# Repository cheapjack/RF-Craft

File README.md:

# RF-Craft

<br>
<br>

RF-Craft is a prototype Raspberry Pi [HAT](https://github.com/raspberrypi/hats) (**H**ardware **A**ttached on **T**op) arduino clone to send `mcpi` API commands wirelessly to a minecraft server. RF-Craft was built as part of Ross Dalziel's [OK Sparks Project](http://domesticscience.org.uk) and a spin-out from the [FACT](http://fact.co.uk/) [CloudMaker](http://www.fact.co.uk/projects/cloudmaker-making-minecraft-real.aspx) project research and inspired by resilient networks, the work of [Martin O'Hanlon](https://github.com/martinohanlon/mcpi) where `mcpi` is maintained via Mojang, [Shrimping.it](http://start.shrimping.it) and Minecraft modders worldwide. 

Full info from the [CloudMaker Repo](https://github.com/cheapjack/CloudMaker)

It is a board to help teach the **Internet of Things** and is inspired by the wider Minecraft community and culture where young people develop their own skillsets in order to take part in the games culture. In many ways it is the first game in mainstream consciousness where players take control of elements of the games infrastructure, independent of the original developer *Mojang*, often becoming their own **sysadmins** using custom servers for games they want to play and as a consequence, with considerable transferable skills in coding and IoT. 

Minecraft is not an open source project but the game community have, in a sense, opened up elements of it to allow extensive modding and creative hacking. This adhoc technical *culture* is what is the most valuable, not the game itself or even it's potential to educate, which is a consequence of this. After a good deal of research we've concluded that Minecraft is more representative of an independent learning culture and ecosystem on it's own and others borrowed terms and with it's own diversity. This is exciting but not necessarily always helpful to educators or learners.  

With experience, we think it should not really be confused with a universal *service* or *platform* that could be easily exploited for formal mainstream education.

Current owners, Microsoft are developing an education *platform* through [Minecraft Education](https://education.minecraft.net/). This is a very specific version of the game and so has very specific requirements to use. In this sense it *is* a platform, but like many platforms in the real world once you are on one its hard to jump to another without ladders, ropes or expensive jetpacks. We've all played on Parkour servers so we know how hard that can be!

We've tried to package up a range of resources, examples and hardware that could allow you to play with connecting versions of the game with the real world with sensors and buttons. 

Finding the right version of the game to experiment with is difficult and has it's own quite steep and confusing learning curve. We recommend keeping it simple and experimenting on a Pi. The Pi version is version 1.0 or something. It's simple and it's not changing. It's also free. There's an established community out there using the python [mcpi API](https://github.com/martinohanlon/mcpi) for it like [Martin O'Hanlon](https://github.com/martinohanlon/) and making cool stuff for it like [PatternCraft](http://patterncraft.co/).

So we've tried keeping it simple by making simple Raspeberry Pi HATS that can transmit and receive serial messages which you can parse into commands in the Raspberry Pi version of Minecraft you can make simpel HelloWorld Text Adventures, [Models of Railways](https://github.com/cheapjack/RF-Rail-Craft) or all the way up to interacting with [data](https://github.com/cheapjack/MoT), the [International Space Station](https://github.com/astro-pi/SpaceCRAFT) to punchard readers that make music just like PatternCraft.

This Open source Radio messaging system uses the [RFM69HW tranceiver chip](https://lowpowerlab.com/shop/rfm69hw)(based on the Lowpowerlab Moteino) and Frequency 868MHz to report to a central reciever to perform minecraft actions.

Its designed as a Minecraft-of-Things deluxe development board bridging the gap between Pi and Arduino without depending on both. One design parameter was to have good signal penetration through Victorian concrete and the concrete of many arts centres and/or schools for the [Ok Sparks!](http://slyrabbit.net/ok-sparks) project by [Domestic Science](http://domesticscience.org.uk). 

It was designed by artist [Ross Dalziel](http://cheapjack.org.uk) and open source engineer and technician in residence at [DoESLiverpool](http://doesliverpool.com) [Patrick Fenner AKA @DefProc](http://www.deferredprocrastination.co.uk/) and funded by [FACT](http://fact.co.uk/) and  [IT as a Utility (ITaaU) Network](http://www.itutility.ac.uk) for the [CloudMaker](http://www.fact.co.uk/projects/cloudmaker-making-minecraft-real.aspx) project following 2 years of research into the game as a social learning tool which we've since realised is, as we've said, more like a *culture*

### Features

 * On board button and LED, 
 * Digital input for a Dallas DS18B20 one-wire temperature sensor (with pullup resistor) and power rail 
 * 6 analog inputs broken out with power
 * Battery power breakout
 * Pi/External mode jumpers
 * IDE Free reciever/transmitter/Node programming switch
 * It can act as a powered HAT reciever/transmitter on board a Pi or as an independent battery powered arduino radio receiver or transmitter.
 * Open Source: Not cheap but open; but you can build them yourself!
 * Good singnal penetration through concrete castles
 * Need IoT Minecraft workshop & WiFi Down? Network Administrator at lunch? Got Pi, Got HAT Got RF-Craft - no problem!
 * Need radio arduinos for IoT prototype? Sick of Minecraft? Caps falling out of your shrimp? No problem use elsewhere!
 * Send Commands to a Receiver HAT and your Raspbians local Minecraft Pi Edition server
 * Send Commands to the Rasperry Juice Plugin on a CanaryMod server
 * Send Commands to the Rasperry Juice Plugin on `mc.fact.co.uk:25589`

### Message Format

messages are constructed of a `uint8_t` for node_id, followed by an `int8_t` for action

Possible action messages:

 * -1 : set_id
 *  0 : query_id
 *  1 : button press
 *  2 : error
 *  3 : OK

common key for messages: "changemechangeme"

all radios are in group: 87

Transmitter `node_ids` for buttons can be 1-100 but the onboard `node_id` switch can set them to 1-15 in Binary. By default with the big mode switch set to **EXT** the HAT is in transmitter mode and you need to set the `node_id` switch to 1-15. When the mode switch is set to **RPI** then the `node_id` is 254 which is a receiver. 

### Getting Started

The easiest thing to do is clone this repo into your `/home/pi` folder either with git or `wget https://github.com/cheapjack/RF-Craft/archive/master.zip` then `unzip`

You can install git with `sudo apt-get install git-core`
Then `git clone https://github.com/cheapjack/RF-Craft.git`

Then you can modify the `HelloPi.py` or `HelloSerial.py` `python 2.7` code and play with the transmitter and receiver boards pairs out of the box without even having to put the arduino sketches on. Unless you're making them yourselves from the details in the repo then well it's your box.

Then for full details you can read the nearby `GettingStarted.md` file

### RF-Craft

### Background

[The Minecraft Of Things](http://minecraftofthings.tumblr.com) sprang from research with [FACT](http://fact.co.uk/), [Dr Mark Wright](https://twitter.com/dr_mark_wright), [Adrian McEwen](http://www.mcqn.com/) and Paul Harter of [PrintCraft](http://www.printcraft.org/) funded by [IT as a Utility (ITaaU) Network](http://www.itutility.ac.uk) for the [CloudMaker](http://www.fact.co.uk/projects/cloudmaker-making-minecraft-real.aspx) project

Looking into how the Raspberry Pi could be used as an entry into embedded systems, physical computing and the Internet Of Things(IoT) we developed something that could be used in many contexts with simplicity at its core and with ideas that touched on data literacy, resilient networks and security. 

One of the big issues with use of Minecraft in education is networking often educators dont have the time or access to setup a school network for a wireless sensors to communicate with the game; we wanted to be able to be independent of this and for people to setup their own adhoc networks to follow how networks are used in real world applications.

For the final distribution of CloudMaker research we focussed on packaging up resources to help understand the Internet Of Things through Minecraft.

We took diverse approaches to reflect real IoT ecosystems; tried not to re-invent the wheel but point to fascinating education work going on in technology and post 'Maker' culture. 

We made simple arduino on a breadboard interfaces inspired by [Shrimping.It](http://start.shrimping.it) for interacting with minecraft over wired USB/FTDI adaptors, [ShrimpCraft](https://github.com/cheapjack/ShrimpCraft), a WiFi on a breadboard system [Cockle-Craft-of-Things](https://github.com/mcqn/cocklecraft-of-things) with MCQN Ltd. 

For RF-Craft we made a super robust custom PCB arduino RFM69 clone that has a more plug & python & play approach.

The receiver button pairs allow you to send wireless messages to a range of minecraft servers for augmented reality gaming and learning the Internet of Things (IoT) 

### Resources

This uses Martin O'Hanlon's [mcpi API](https://github.com/martinohanlon/mcpi) the Minecraft: Pi Edition API Python Library and his and Zhuowei's [Canary Raspberry Juice](https://github.com/martinohanlon/CanaryRaspberryJuice) plugin for use with FACT's CloudMaker Minecraft Server

### The FACT Server

The FACT CloudMaker Server is a server for prototyping multiplayer `mcpi` activity. Details for how to log on are at the [CloudMaker portal repo](https://github.com/cheapjack/CloudMaker/)

#### Plugins

 * Printbot
 * ScriptCraft
 * WorldEdit
 * Essentials

You can view the [Minecraft CloudMaker Server with this link](http://89.34.96.47:8125/)

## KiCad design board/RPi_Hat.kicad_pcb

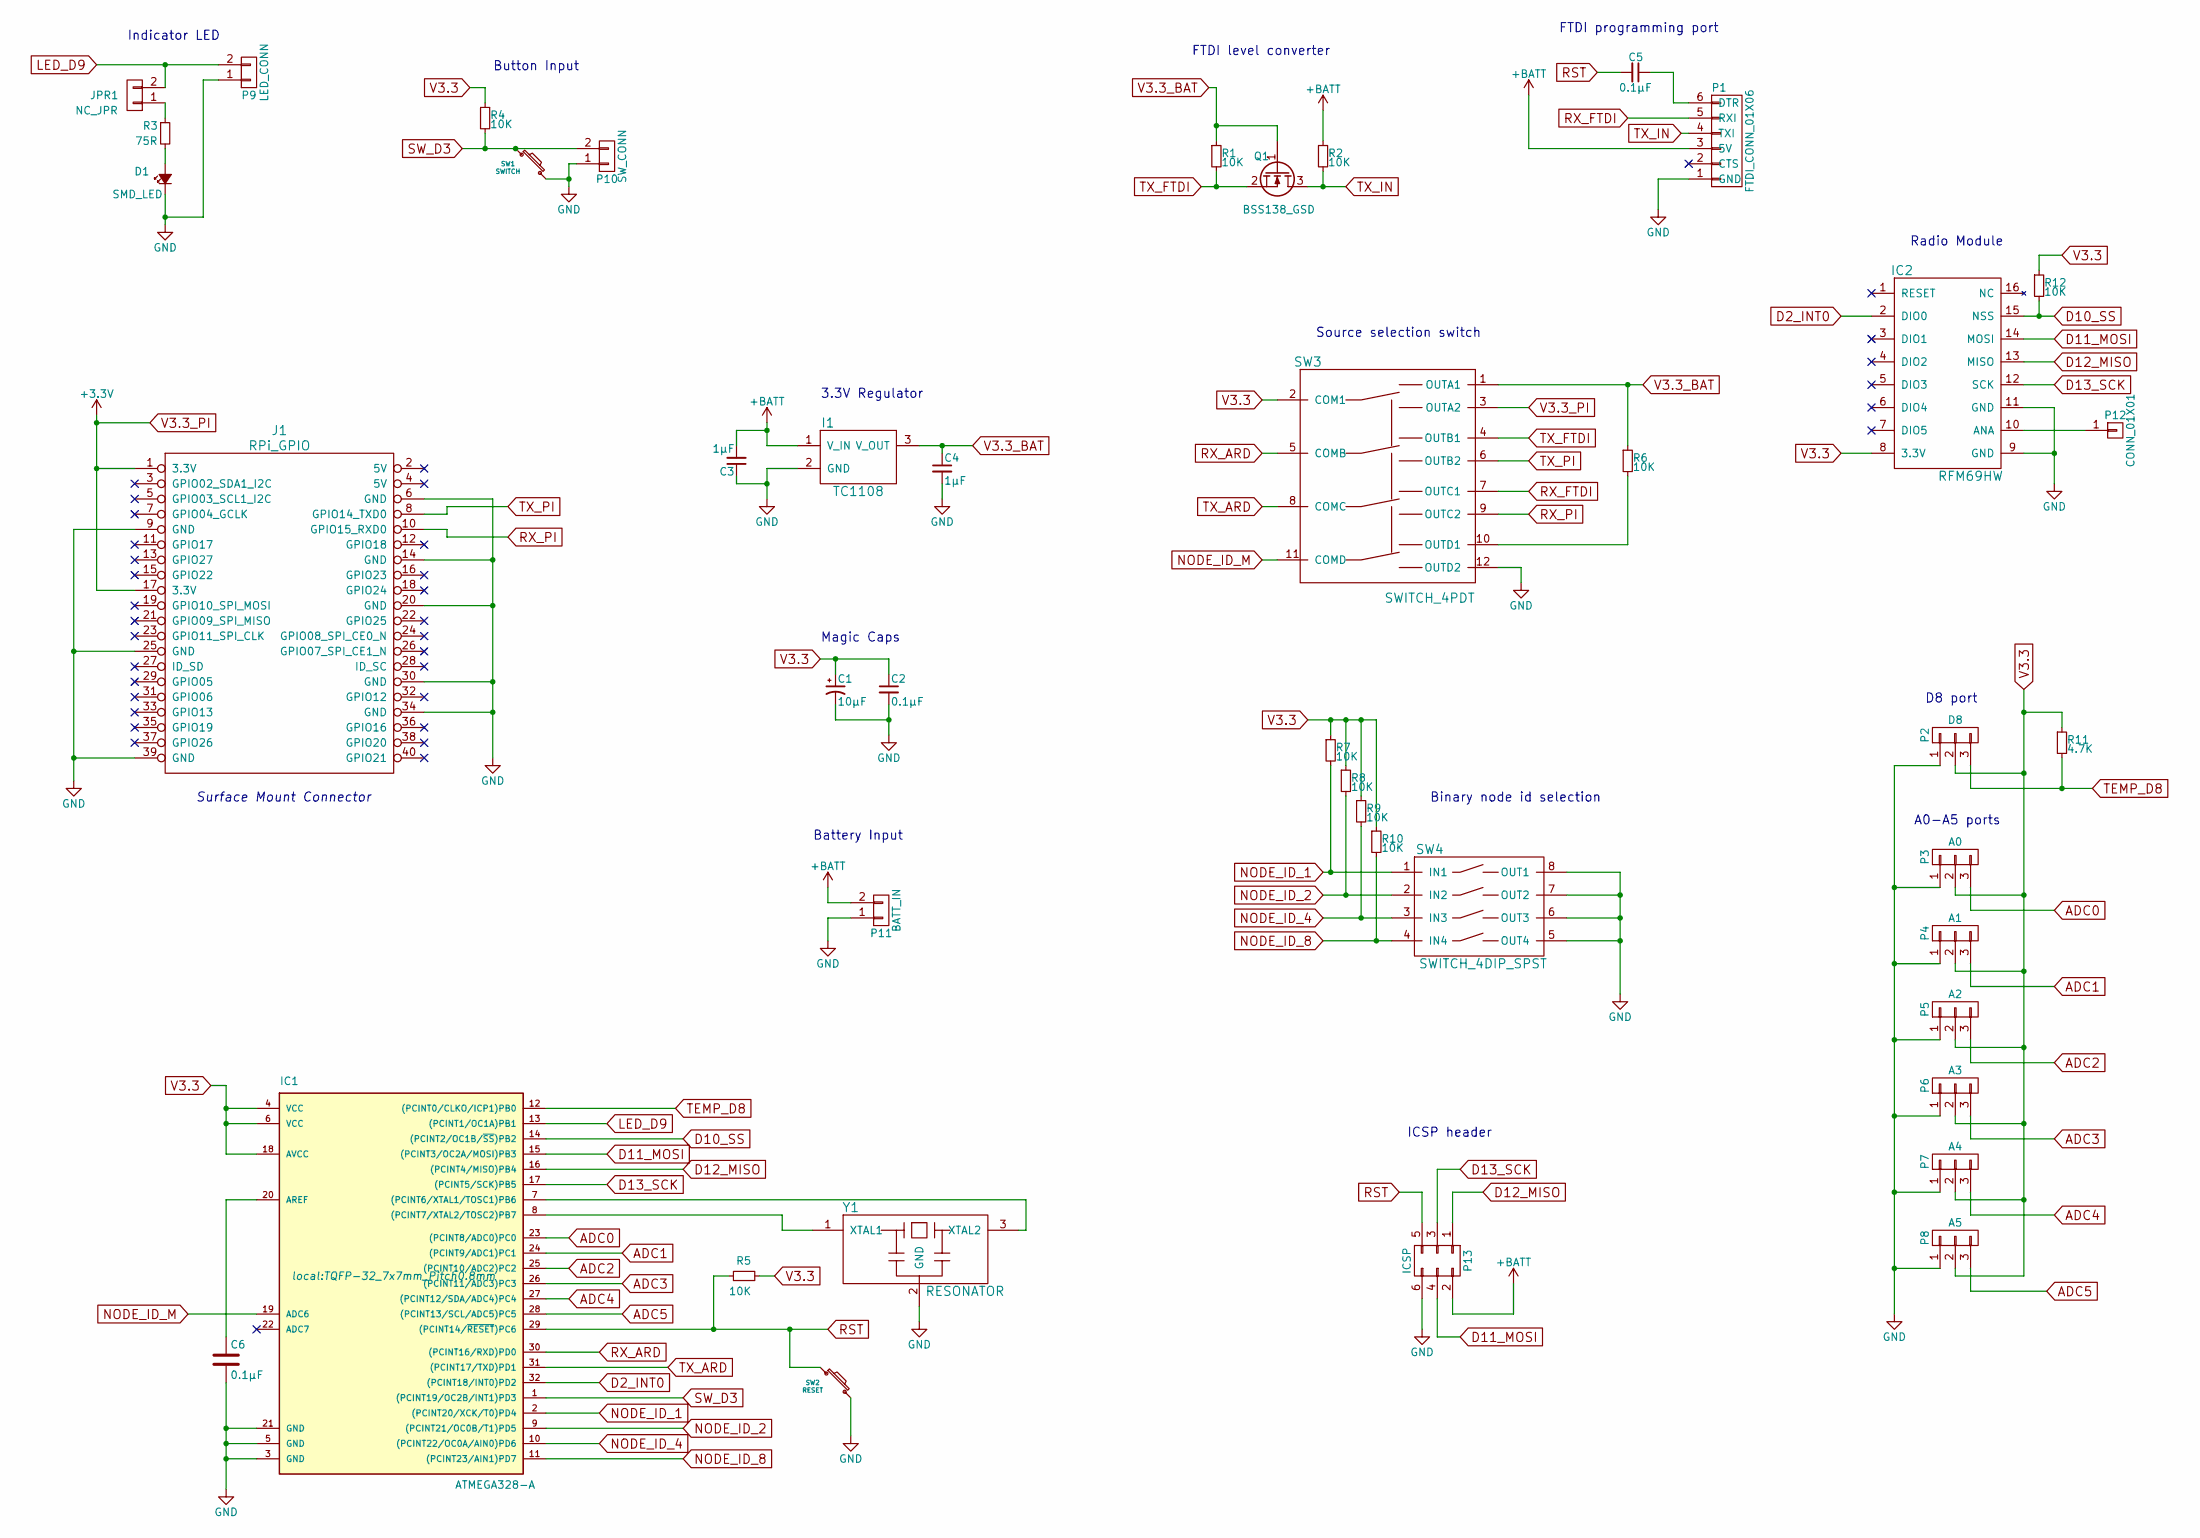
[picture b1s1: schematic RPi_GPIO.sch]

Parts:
C1: 10µF; c_elec_3x5.3
C2, C5, C6: 0.1µF; C_0805_HandSoldering
C3, C4: 1µF; C_1206_HandSoldering
D1: SMD_LED; LED_1206
I1: TC1108; SOT-223
IC1: ATMEGA328-A; TQFP-32_7x7mm_Pitch0.8mm
IC2: RFM69HW; RFM69
J1: RPi_GPIO; Samtec_HLE-120-02-XXX-DV-BE-XX-XX
JPR1: NC_JPR; NC_SMD_JPR
P1: FTDI_CONN_01X06; Pin_Header_Straight_1x06
P2: D8; Pin_Header_Straight_1x03
P3: A0; Pin_Header_Straight_1x03
P4: A1; Pin_Header_Straight_1x03
P5: A2; Pin_Header_Straight_1x03
P6: A3; Pin_Header_Straight_1x03
P7: A4; Pin_Header_Straight_1x03
P8: A5; Pin_Header_Straight_1x03
P9: LED_CONN; Pin_Header_Straight_1x02
P10: SW_CONN; Pin_Header_Straight_1x02
P11: BATT_IN; bornier2
P12: CONN_01X01; Pin_Header_Straight_1x01
P13: ICSP; ISCP_header
Q1: BSS138_GSD; SOT-23_Handsoldering
R1, R2, R4, R5, R6, R7, R8, R9, R10, R12: 10K; R_0603_HandSoldering
R3: 75R; R_0603_HandSoldering
R11: 4.7K; R_0603_HandSoldering
SW1: SWITCH; KSEx00G_SW
SW2: RESET; KSEx00G_SW
SW3: SWITCH_4PDT; SWITCH_4PDT_MFS401N
SW4: SWITCH_4DIP_SPST; SW_DIP_04_GULL_BINARY
Y1: RESONATOR; Resonator_3.2x1.3

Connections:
+BATT: C3.2, I1.1 (V_IN), P1.3 (5V), P11.2, P13.2, R2.1
ADC0: IC1.23 ((PCINT8/ADC0)PC0), P3.3
ADC1: IC1.24 ((PCINT9/ADC1)PC1), P4.3
ADC2: IC1.25 ((PCINT10/ADC2)PC2), P5.3
ADC3: IC1.26 ((PCINT11/ADC3)PC3), P6.3
ADC4: IC1.27 ((PCINT12/SDA/ADC4)PC4), P7.3
ADC5: IC1.28 ((PCINT13/SCL/ADC5)PC5), P8.3
D2_INT0: IC1.32 ((PCINT18/INT0)PD2), IC2.2 (DIO0)
D10_SS: IC1.14 ((PCINT2/OC1B/~SS~)PB2), IC2.15 (NSS), R12.2
D11_MOSI: IC1.15 ((PCINT3/OC2A/MOSI)PB3), IC2.14 (MOSI), P13.4
D12_MISO: IC1.16 ((PCINT4/MISO)PB4), IC2.13 (MISO), P13.1
D13_SCK: IC1.17 ((PCINT5/SCK)PB5), IC2.12 (SCK), P13.3
GND: C1.2, C2.2, C3.1, C4.2, C6.2, D1.1 (K), I1.2 (GND), IC1.3 (GND), IC1.5 (GND), IC1.21 (GND), IC2.9 (GND), IC2.11 (GND), J1.6 (GND), J1.9 (GND), J1.14 (GND), J1.20 (GND), J1.25 (GND), J1.30 (GND), J1.34 (GND), J1.39 (GND), P1.1 (GND), P2.1, P3.1, P4.1, P5.1, P6.1, P7.1, P8.1, P9.1, P10.1, P11.1, P13.6, SW1.2, SW2.2, SW3.12 (OUTD2), SW4.5 (OUT4), SW4.6 (OUT3), SW4.7 (OUT2), SW4.8 (OUT1), Y1.2 (GND)
LED_D9: IC1.13 ((PCINT1/OC1A)PB1), JPR1.2, P9.2
NODE_ID_1: IC1.2 ((PCINT20/XCK/T0)PD4), R7.2, SW4.1 (IN1)
NODE_ID_2: IC1.9 ((PCINT21/OC0B/T1)PD5), R8.2, SW4.2 (IN2)
NODE_ID_4: IC1.10 ((PCINT22/OC0A/AIN0)PD6), R9.2, SW4.3 (IN3)
NODE_ID_8: IC1.11 ((PCINT23/AIN1)PD7), R10.2, SW4.4 (IN4)
NODE_ID_M: IC1.19 (ADC6), SW3.11 (COMD)
unnamed: C5.1, P1.6 (DTR)
unnamed: C6.1, IC1.20 (AREF)
unnamed: D1.2 (A), R3.2
unnamed: IC1.7 ((PCINT6/XTAL1/TOSC1)PB6), Y1.3 (XTAL2)
unnamed: IC1.8 ((PCINT7/XTAL2/TOSC2)PB7), Y1.1 (XTAL1)
unnamed: IC2.10 (ANA), P12.1
unnamed: JPR1.1, R3.1
unnamed: R6.2, SW3.10 (OUTD1)
RST: C5.2, IC1.29 ((PCINT14/~RESET~)PC6), P13.5, R5.1, SW2.1
RX_ARD: IC1.30 ((PCINT16/RXD)PD0), SW3.5 (COMB)
RX_FTDI: P1.5 (RXI), SW3.7 (OUTC1)
RX_PI: J1.10 (GPIO15_RXD0), SW3.9 (OUTC2)
SW_D3: IC1.1 ((PCINT19/OC2B/INT1)PD3), P10.2, R4.2, SW1.1
TEMP_D8: IC1.12 ((PCINT0/CLKO/ICP1)PB0), P2.3, R11.2
TX_ARD: IC1.31 ((PCINT17/TXD)PD1), SW3.8 (COMC)
TX_FTDI: Q1.2 (S), R1.2, SW3.4 (OUTB1)
TX_IN: P1.4 (TXI), Q1.3 (D), R2.2
TX_PI: J1.8 (GPIO14_TXD0), SW3.6 (OUTB2)
V3.3: C1.1, C2.1, IC1.4 (VCC), IC1.6 (VCC), IC1.18 (AVCC), IC2.8 (3.3V), P2.2, P3.2, P4.2, P5.2, P6.2, P7.2, P8.2, R4.1, R5.2, R7.1, R8.1, R9.1, R10.1, R11.1, R12.1, SW3.2 (COM1)
V3.3_BAT: C4.1, I1.3 (V_OUT), Q1.1 (G), R1.1, R6.1, SW3.1 (OUTA1)
V3.3_PI: J1.1 (3.3V), J1.17 (3.3V), SW3.3 (OUTA2)

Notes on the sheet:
Surface Mount Connector
Battery Input
FTDI programming port
FTDI level converter
Source selection switch
3.3V Regulator
Magic Caps
Indicator LED
Button Input
Radio Module
A0-A5 ports
Binary node id selection
D8 port
ICSP header

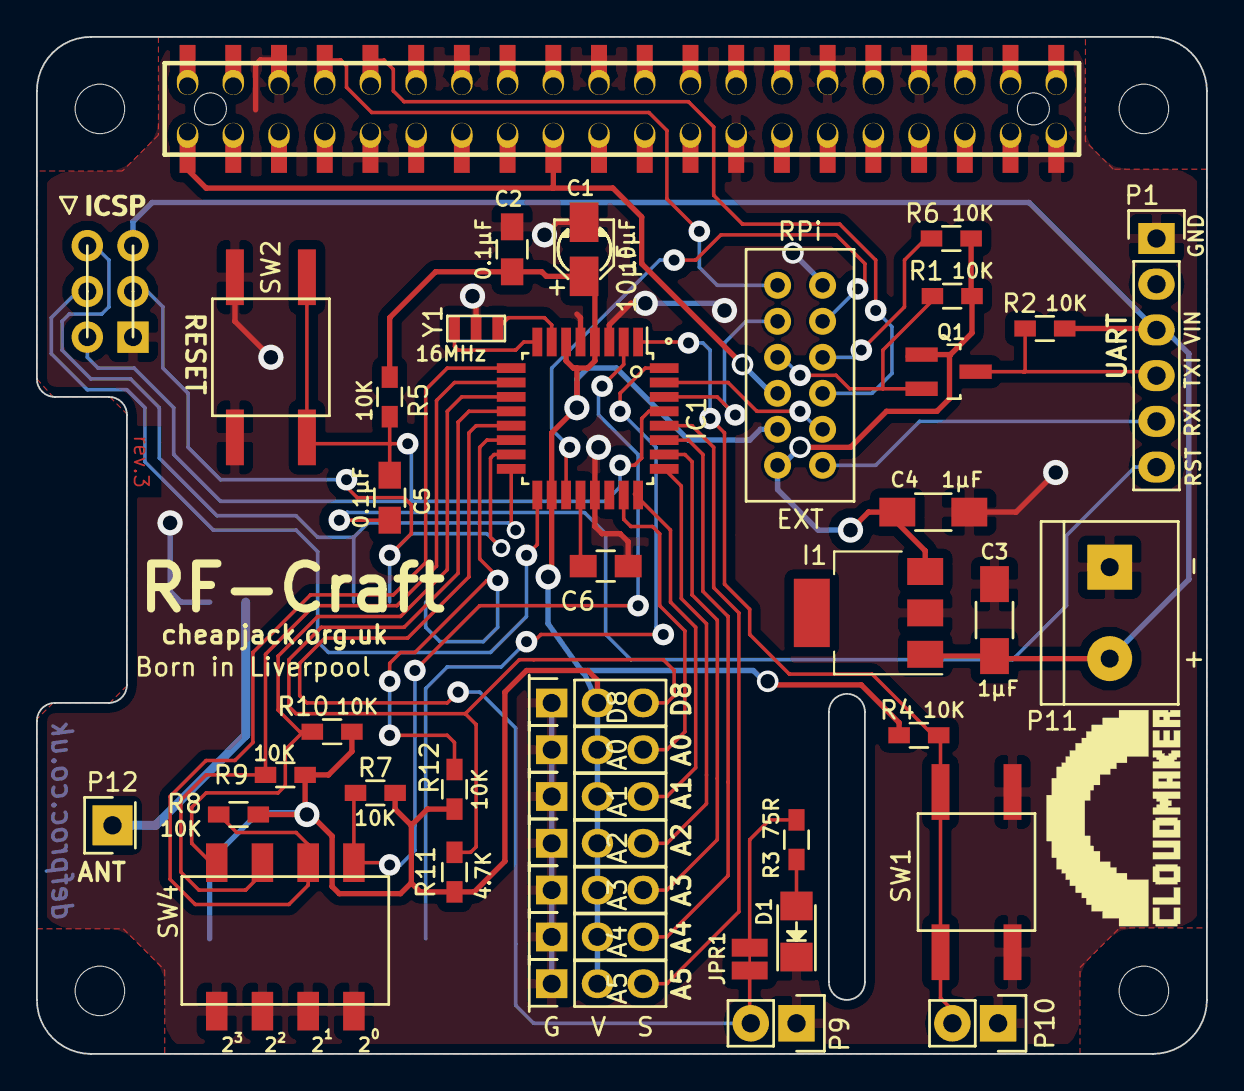
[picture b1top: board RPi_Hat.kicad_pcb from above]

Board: 2 copper layers, 65.0 x 56.5 mm, 43 parts (1 on the bottom side), 40 nets.

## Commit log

2015-08-05 first working versions of the button and receiver codes
2015-09-21 incoming serial strings are now parsed for replies
2015-09-21 readme formatting
2015-09-22 documentation for parts
2015-10-01 gitignore for ano and kicad
2015-10-01 first draft of HAT shape board and schematic
2015-10-01 included bidirectional logic level converter
2015-10-02 first draft of the HAT layout
2015-10-02 resonator and led datasheets
2015-10-05 changed arduino-IDE friendly files to hard links
2015-10-05 removed swap files and added them to the gitignore
2015-10-05 updated the python code
2015-10-05 board layout. check before manufacture
2015-10-05 datasheet for push button switch
2015-10-05 changed LED resistor to 75ohms (0603 package)
2015-10-06 checked vias and rerouted a 3.3V line. Ready for manufacture
2015-10-06 gerbers for manufacture (rev.1 pcb)
2015-10-06 added missing parts docs
2015-10-06 xml updates
2015-10-06 included BoM for rev1
2015-10-12 revised via sizes, as per board house recommendations
2015-10-12 revised gerbers for b72ee2
2015-10-12 deleted and regenerated gerbers to be sure
2015-10-12 updated gitignore for kicad autosaves and gerber zips
2015-10-21 case draft
2015-10-22 parts and costs sheet
2015-10-26 platformio inits and ignores
2015-10-26 added SPI to RFM69 lib
2015-10-26 changed code for QUERY_ID and SET_ID, and allowed setting id
2015-10-27 added moteino (on ttyUSB0) build targets for platformio
2015-10-27 added morse flashing for response
2015-10-27 changed serial responses to ACK/NAK/ERROR
2015-10-27 added serial parsing and node id specification to button code
    but I had to comment out the sleep code for now
2015-10-29 updated parts list
2015-10-29 added an svg to eps makefile for easier creation
2015-10-29 panellised cut files for the case
2015-10-29 ignored output eps files in the case directory
2015-11-26 morse outgoing messages using the onboard LED
2016-03-18 Added RF-Craft.py, server.py and amended button-hello.py and button-test.py
2016-05-05 fixed 3.3v error, and button rotation bug
2016-05-06 gerbers and rev1.2 board text
2016-05-06 corrected the reduced solder mask on jumpers
2016-05-17 moved platformio structure to it's own folder and removed spi call in receiver
2016-05-17 changed arduino files to hardlinks (so arduino IDE doesn't follow)
2016-05-17 Modified .gitignore to include .DS_Store
2016-05-17 Modified serial find to single quotes
2016-05-24 Updated all READMEs and code ready for workshop
2016-05-24 Fixed Markdown in code refs
2016-06-09 Fixed default button to listen to to ID 1 and made clearer README.md background text
2016-06-09 Added Arduino editing instructions for receivers and buttons
2016-06-09 Updated API Ref markdown
2016-07-01 solid logo, and 12mm kicad module of it
2016-07-05 moved Samtec footprint into project library
2016-07-05 resonator, analog input bank, source switch
2016-07-05 include cloudmaker.pretty library for this project
2016-07-05 footprint and documentation for the 4PDT source selector switch
2016-07-05 added node ID selection 4-way DIP switches
2016-07-06 ISCP header and footprint assignments
2016-07-06 fixed some old (out of date) footprint assignments
2016-07-06 corrections to netlist
2016-07-06 draft of rev.2 routed
2016-07-06 board edited and ready for manual checks rev.2.rc1
2016-07-06 changed FTDI to UART
2016-07-07 upped the via pad anualar ring from 7.8thou to 11.8thou (+0.1mm)
2016-07-07 moved to double sided rpi header footprint
2016-07-07 gerbers for rev.2 board
2016-07-28 rev.2 solder mask svg for laser cutting
2016-07-29 added dip and slide switch check and combined gateway and button code
2016-07-29 and included the gateway's light flashing on receive
2016-08-01 reduced atmega soldermask area to 80% of original
2016-08-01 new blink sketch for the onboard led
2016-08-01 added startup blink for the onboard led
2016-08-02 Documentation of the Cooking and Assembly Process
2016-08-02 reinitialise the radio on node id change
2016-12-20 Used a more realistic license and added some thought around culture
2016-12-20 Added new image in README.md
2016-12-20 fixed image positions
2016-12-20 License fix
2016-12-20 Added the necessary Arduino libraries to add to users Arduino Sketchbook
2016-12-21 Moved libraries to similar location as Shrimping.It so changing the arduino sketchbook to arduino will make it easier to find libraries in the sketches
2016-12-28 up to date with remote
2016-12-28 Revert "up to date with remote"
    This reverts commit 92056238b58dd1545c72053bc3b2b9ea0aa8e0b0.
2017-01-04 added missing schematic parts lib
2017-01-04 schematic and netlist changes for issues 1–5
2017-01-04 rev3 board draft
2017-01-04 draft BOM
2017-01-06 tweaked the text in the logo to avoid bleeding on the print
2017-01-12 new logo, and rev3 layout
2017-02-27 Updated HelloSerial.py
2017-02-27 Added info on prepping Pi for HATs for the changes to Raspbian 2016-03-18 onwards
2017-02-27 Added credit to Frederick Vanbenbosch for Serial HAT fix
2017-02-27 Added extra fool proof details
2017-02-27 Made way for a new GettingStarted.md
2017-02-28 Added thoughts on culture and fixed the dynmap link and port
2017-02-28 added build guide pdf
2017-03-05 New getting started guide
2017-03-05 Added testing how to with screen
2017-03-06 updated and fixed ports and typos
2017-03-08 Fixed spacing and code inserts in APIRef for Joseph
2021-06-03 fixed BoM mission colomn
